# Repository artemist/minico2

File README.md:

# minico2

A simple CO2 monitor based on the Sensirion SCD-30 and an ESP32. This is intended to have Wi-Fi and Ethernet
thought that is not yet implemented

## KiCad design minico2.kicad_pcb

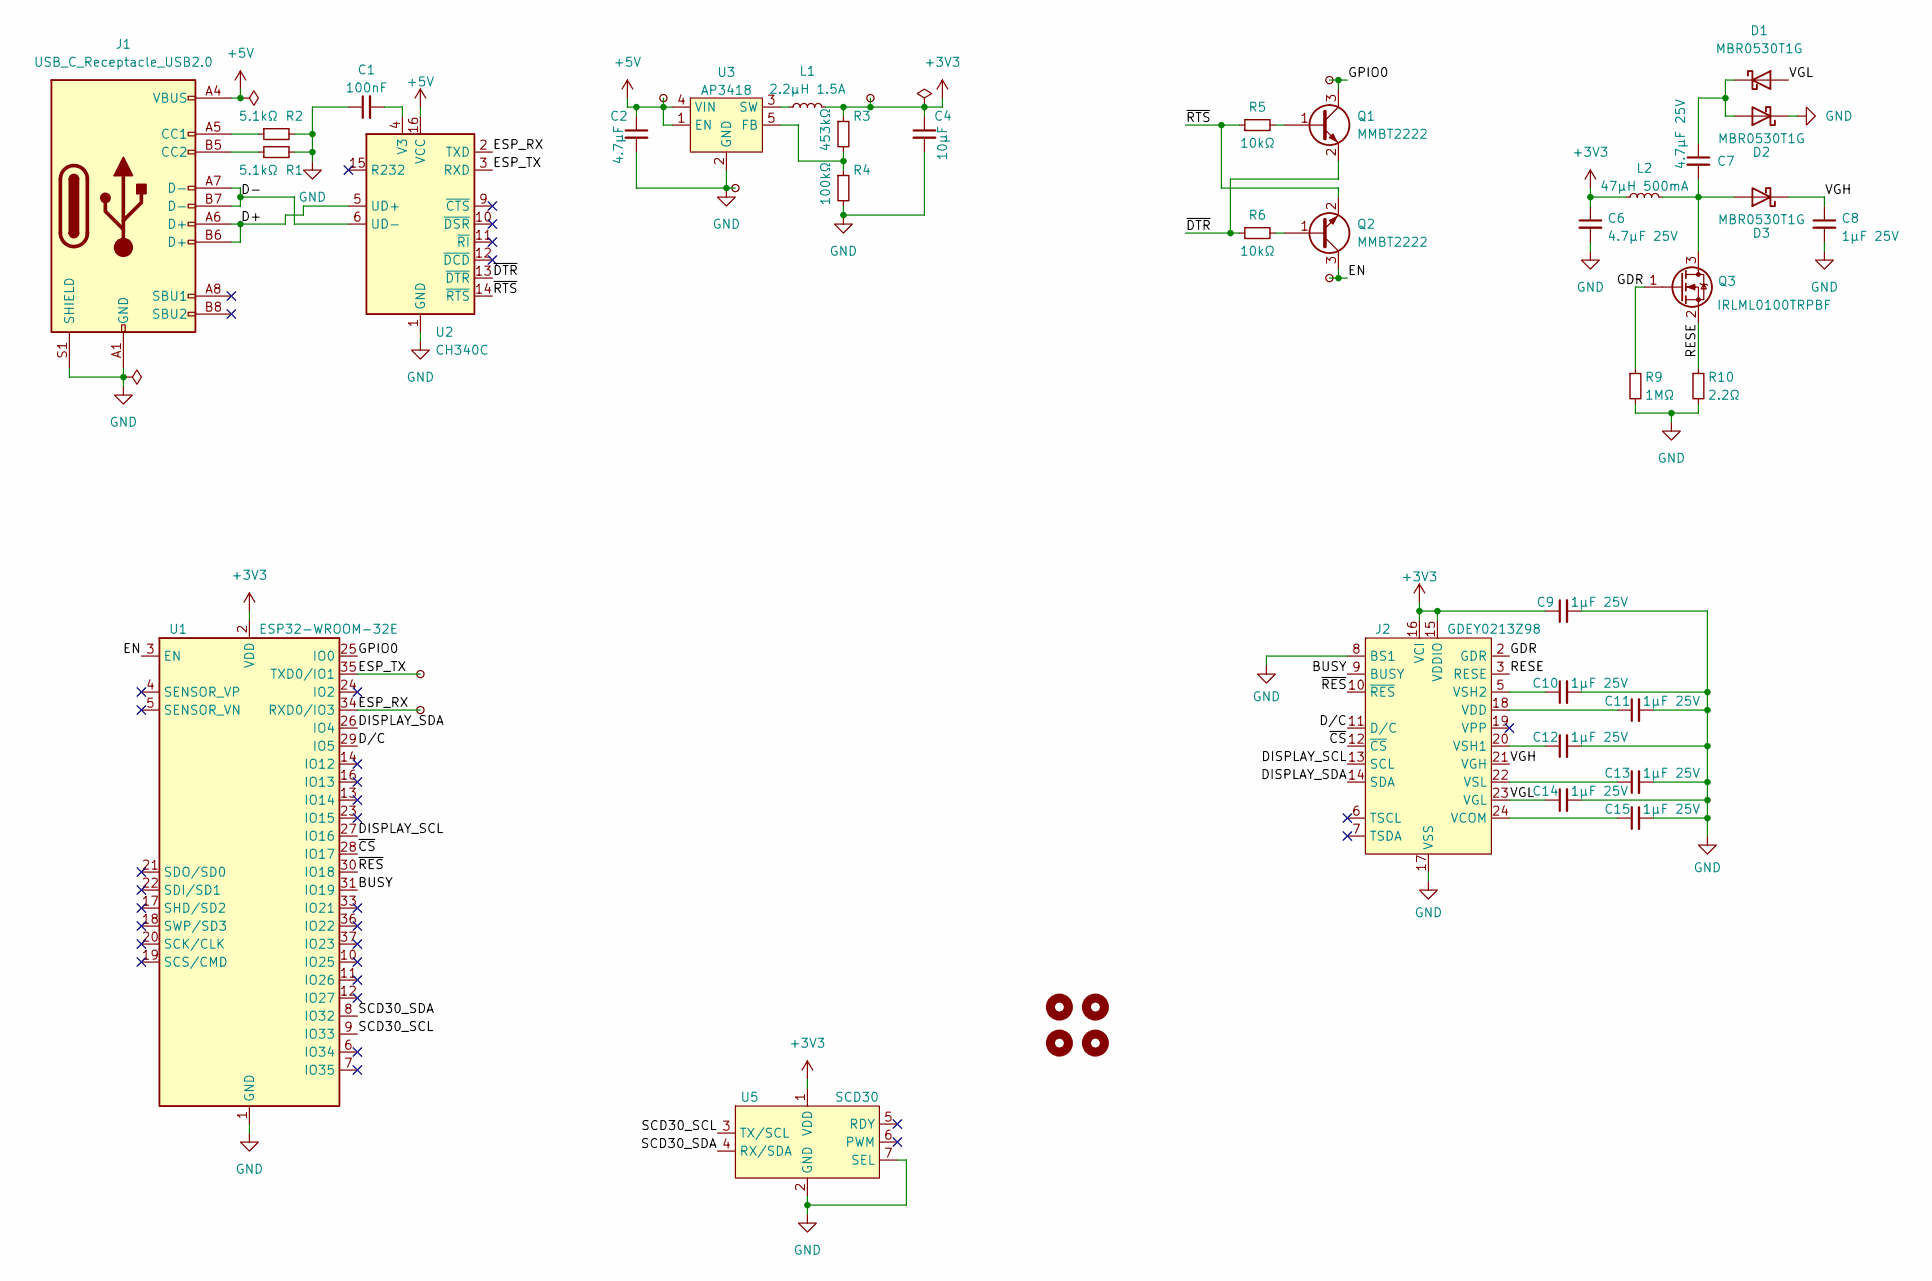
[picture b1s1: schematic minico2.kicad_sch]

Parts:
C1: 100nF; C_0603_1608Metric
C2: 4.7µF; C_0603_1608Metric
C4: 10µF; C_0603_1608Metric
C6, C7: 4.7µF 25V; C_0603_1608Metric
C8, C9, C10, C11, C12, C13, C14, C15: 1µF 25V; C_0603_1608Metric
D1, D2, D3: MBR0530T1G; D_SOD-123
H1, H2, H3, H4: MountingHole; MountingHole_2.7mm_M2.5
J1: USB_C_Receptacle_USB2.0; USB_C_Receptacle_HRO_TYPE-C-31-M-12
J2: GDEY0213Z98; JUSHUO_AFC07-S24ECC-00_1x24-1MP_P0.5mm_Horizontal_Reversed_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
L1: 2.2µH 1.5A; L_1008_2520Metric
L2: 47µH 500mA; L_Taiyo-Yuden_NR-60xx
Q1, Q2: MMBT2222; SOT-23
Q3: IRLML0100TRPBF; SOT-23
R1, R2: 5.1kΩ; R_0603_1608Metric
R3: 453kΩ; R_0603_1608Metric
R4: 100kΩ; R_0603_1608Metric
R5, R6: 10kΩ; R_0603_1608Metric
R9: 1MΩ; R_0603_1608Metric
R10: 2.2Ω; R_0603_1608Metric
TP1, TP2, TP3: TestPoint_Small; TestPoint_Pad_D2.0mm
TP4, TP5, TP6, TP7: TestPoint_Small; TestPoint_Pad_D1.0mm
U1: ESP32-WROOM-32E; ESP32-WROOM-32
U2: CH340C; SOIC-16_3.9x9.9mm_P1.27mm
U3: AP3418; SOT-25
U5: SCD30; scd30

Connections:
+3V3: C4.1, C6.1, C9.1, J2.15 (VDDIO), J2.16 (VCI), L1.2, L2.1, R3.1, TP3.1, U1.2 (VDD), U5.1 (VDD)
+5V: C2.1, J1.A4 (VBUS), J1.A9 (VBUS), J1.B4 (VBUS), J1.B9 (VBUS), TP2.1, U2.16 (VCC), U3.1 (EN), U3.4 (VIN)
/BUSY: J2.9 (BUSY), U1.31 (IO19)
/D+: J1.A6 (D+), J1.B6 (D+), U2.5 (UD+)
/D-: J1.A7 (D-), J1.B7 (D-), U2.6 (UD-)
/DISPLAY_SCL: J2.13 (SCL), U1.27 (IO16)
/DISPLAY_SDA: J2.14 (SDA), U1.26 (IO4)
/D/C: J2.11 (D/C), U1.29 (IO5)
/EN: Q2.3 (C), TP5.1, U1.3 (EN)
/ESP_RX: TP7.1, U1.34 (RXD0/IO3), U2.2 (TXD)
/ESP_TX: TP6.1, U1.35 (TXD0/IO1), U2.3 (RXD)
/GDR: J2.2 (GDR), Q3.1 (G), R9.1
/GPIO0: Q1.3 (C), TP4.1, U1.25 (IO0)
/RESE: J2.3 (RESE), Q3.2 (S), R10.1
/SCD30_SCL: U1.9 (IO33), U5.3 (TX/SCL)
/SCD30_SDA: U1.8 (IO32), U5.4 (RX/SDA)
/VGH: C8.1, D3.1 (K), J2.21 (VGH)
/VGL: C14.1, D1.2 (A), J2.23 (VGL)
/~CS: J2.12 (~CS), U1.28 (IO17)
/~DTR: Q1.2 (E), R6.1, U2.13 (~DTR)
/~RES: J2.10 (~RES), U1.30 (IO18)
/~RTS: Q2.2 (E), R5.1, U2.14 (~RTS)
GND: C1.1, C2.2, C4.2, C6.2, C8.2, C9.2, C10.2, C11.2, C12.2, C13.2, C14.2, C15.2, D2.1 (K), J1.A1 (GND), J1.A12 (GND), J1.B1 (GND), J1.B12 (GND), J1.S1 (SHIELD), J2.8 (BS1), J2.17 (VSS), R1.2, R2.2, R4.2, R9.2, R10.2, TP1.1, U1.1 (GND), U1.15 (GND), U1.38 (GND), U1.39 (GND), U2.1 (GND), U3.2 (GND), U5.2 (GND), U5.7 (SEL)
unnamed: C1.2, U2.4 (V3)
unnamed: C7.1, D1.1 (K), D2.2 (A)
unnamed: C7.2, D3.2 (A), L2.2, Q3.3 (D)
unnamed: C10.1, J2.5 (VSH2)
unnamed: C11.1, J2.18 (VDD)
unnamed: C12.1, J2.20 (VSH1)
unnamed: C13.1, J2.22 (VSL)
unnamed: C15.1, J2.24 (VCOM)
unnamed: J1.A5 (CC1), R2.1
unnamed: J1.B5 (CC2), R1.1
unnamed: L1.1, U3.3 (SW)
unnamed: Q1.1 (B), R5.2
unnamed: Q2.1 (B), R6.2
unnamed: R3.2, R4.1, U3.5 (FB)

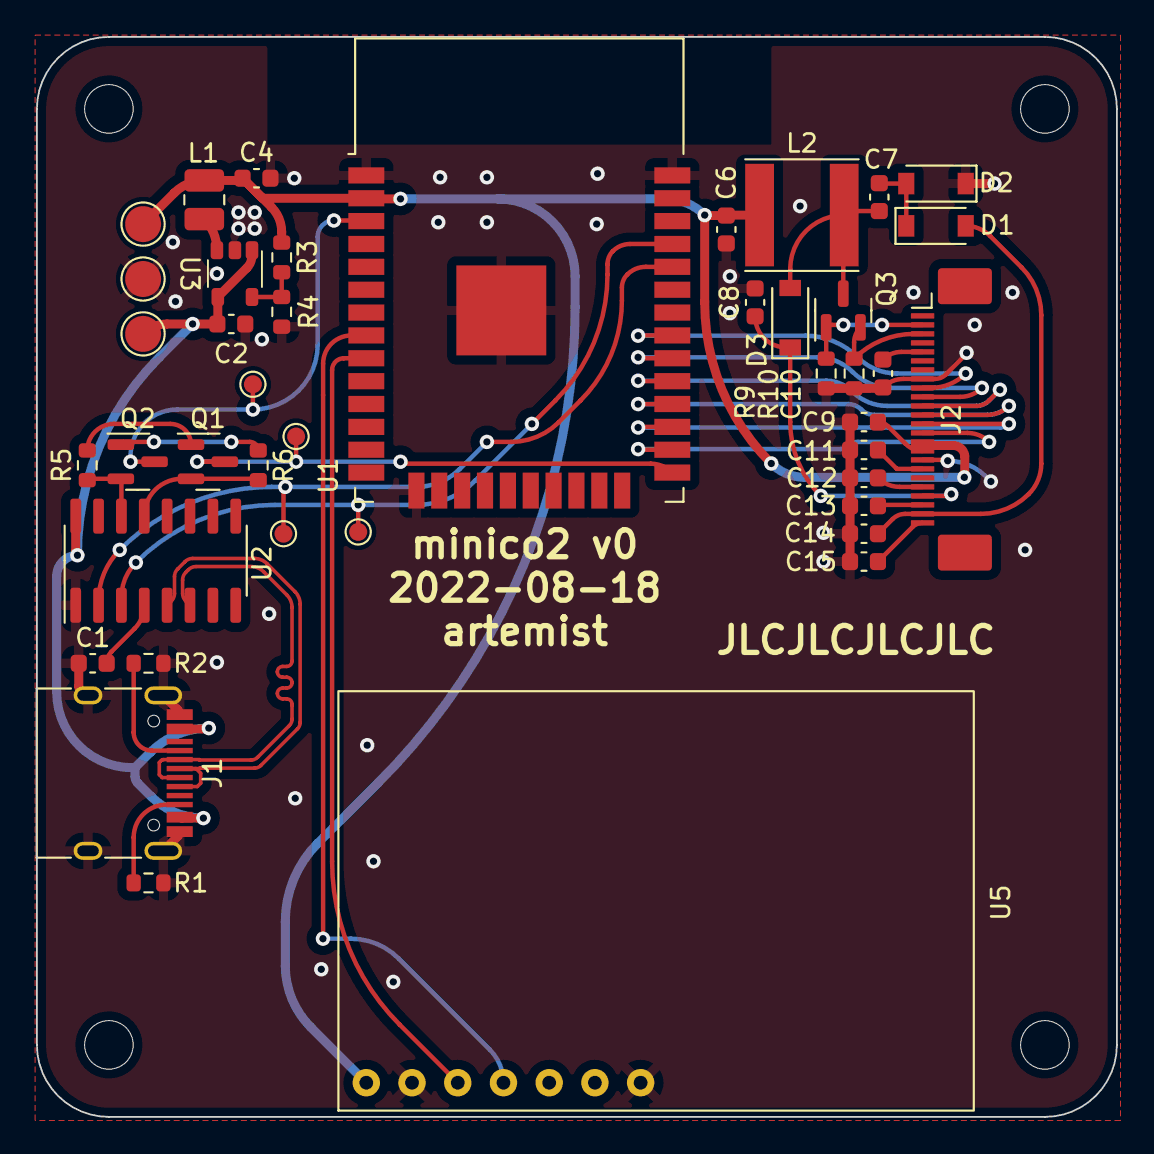
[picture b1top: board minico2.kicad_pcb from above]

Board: 2 copper layers, 60.0 x 60.0 mm, 46 parts (0 on the bottom side), 37 nets.

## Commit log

2022-07-10 Some initial work
2022-07-17 Add support compomenents for display matching datasheet
2022-07-25 Assign footprints
2022-08-17 Add new AP3418 symbol and footprint
2022-08-18 Route PCB
2022-08-18 Fillet some tracks to prepare for production
2022-08-19 Ready for 1st production run
2022-09-11 Start work on battery version
